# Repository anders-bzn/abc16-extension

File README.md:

# abc16-extension
The extension board needed in ABC80x when it shall be used with ABC16

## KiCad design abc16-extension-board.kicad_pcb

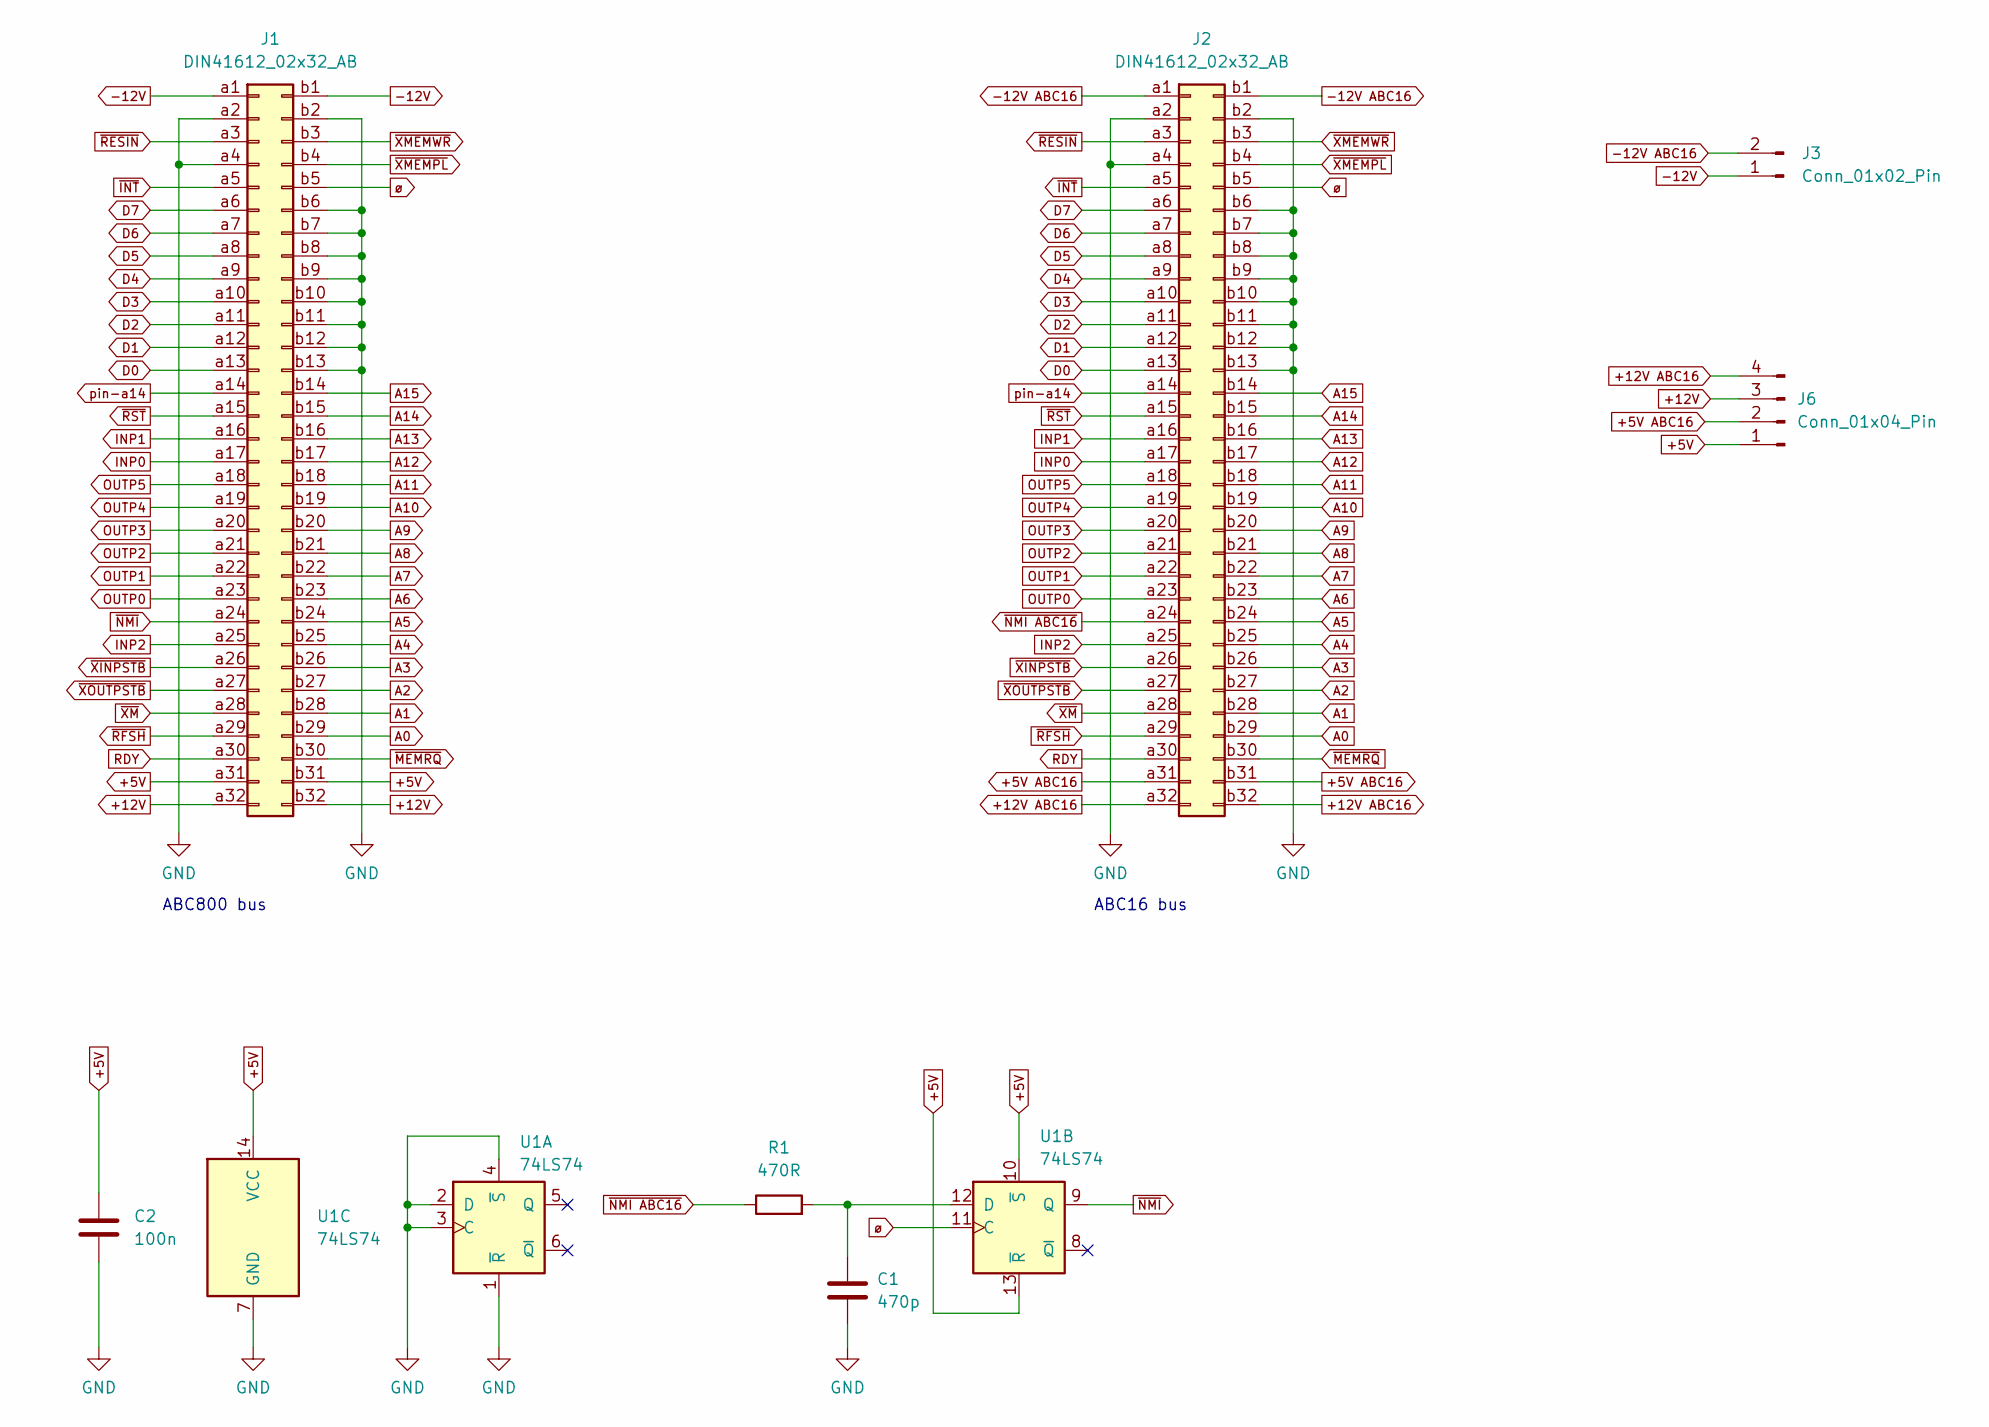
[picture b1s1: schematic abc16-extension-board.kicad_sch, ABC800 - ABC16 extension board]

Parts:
C1: 470p; C_Disc_D3.0mm_W1.6mm_P2.50mm
C2: 100n; C_Rect_L7.2mm_W2.5mm_P5.00mm_FKS2_FKP2_MKS2_MKP2
J1, J2: DIN41612_02x32_AB; DIN41612_B_2x32_Male_Horizontal_THT
J3: Conn_01x02_Pin; PinHeader_1x02_P2.54mm_Vertical
J6: Conn_01x04_Pin; PinHeader_2x02_P2.54mm_Vertical
R1: 470R; R_Axial_DIN0207_L6.3mm_D2.5mm_P10.16mm_Horizontal
U1: 74LS74; DIP-14_W7.62mm

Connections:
+5V: C2.1, J1.a31, J1.b31, J6.1, U1.10 (~S), U1.13 (~R), U1.14 (VCC)
+5V ABC16: J2.a31, J2.b31, J6.2
+12V: J1.a32, J1.b32, J6.3
+12V ABC16: J2.a32, J2.b32, J6.4
-12V: J1.a1, J1.b1, J3.1
-12V ABC16: J2.a1, J2.b1, J3.2
A0: J1.b29, J2.b29
A1: J1.b28, J2.b28
A2: J1.b27, J2.b27
A3: J1.b26, J2.b26
A4: J1.b25, J2.b25
A5: J1.b24, J2.b24
A6: J1.b23, J2.b23
A7: J1.b22, J2.b22
A8: J1.b21, J2.b21
A9: J1.b20, J2.b20
A10: J1.b19, J2.b19
A11: J1.b18, J2.b18
A12: J1.b17, J2.b17
A13: J1.b16, J2.b16
A14: J1.b15, J2.b15
A15: J1.b14, J2.b14
D0: J1.a13, J2.a13
D1: J1.a12, J2.a12
D2: J1.a11, J2.a11
D3: J1.a10, J2.a10
D4: J1.a9, J2.a9
D5: J1.a8, J2.a8
D6: J1.a7, J2.a7
D7: J1.a6, J2.a6
GND: C1.2, C2.2, J1.a2, J1.a4, J1.b2, J1.b6, J1.b7, J1.b8, J1.b9, J1.b10, J1.b11, J1.b12, J1.b13, J2.a2, J2.a4, J2.b2, J2.b6, J2.b7, J2.b8, J2.b9, J2.b10, J2.b11, J2.b12, J2.b13, U1.1 (~R), U1.2 (D), U1.3 (C), U1.4 (~S), U1.7 (GND)
INP0: J1.a17, J2.a17
INP1: J1.a16, J2.a16
INP2: J1.a25, J2.a25
unnamed: C1.1, R1.2, U1.12 (D)
OUTP0: J1.a23, J2.a23
OUTP1: J1.a22, J2.a22
OUTP2: J1.a21, J2.a21
OUTP3: J1.a20, J2.a20
OUTP4: J1.a19, J2.a19
OUTP5: J1.a18, J2.a18
RDY: J1.a30, J2.a30
pin-a14: J1.a14, J2.a14
~INT: J1.a5, J2.a5
~MEMRQ: J1.b30, J2.b30
~NMI ABC16: J2.a24, R1.1
~NMI: J1.a24, U1.9 (Q)
~RESIN: J1.a3, J2.a3
~RFSH: J1.a29, J2.a29
~RST: J1.a15, J2.a15
~XINPSTB: J1.a26, J2.a26
~XMEMPL: J1.b4, J2.b4
~XMEMWR: J1.b3, J2.b3
~XM: J1.a28, J2.a28
~XOUTPSTB: J1.a27, J2.a27
ø: J1.b5, J2.b5, U1.11 (C)

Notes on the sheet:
ABC800 bus
ABC16 bus

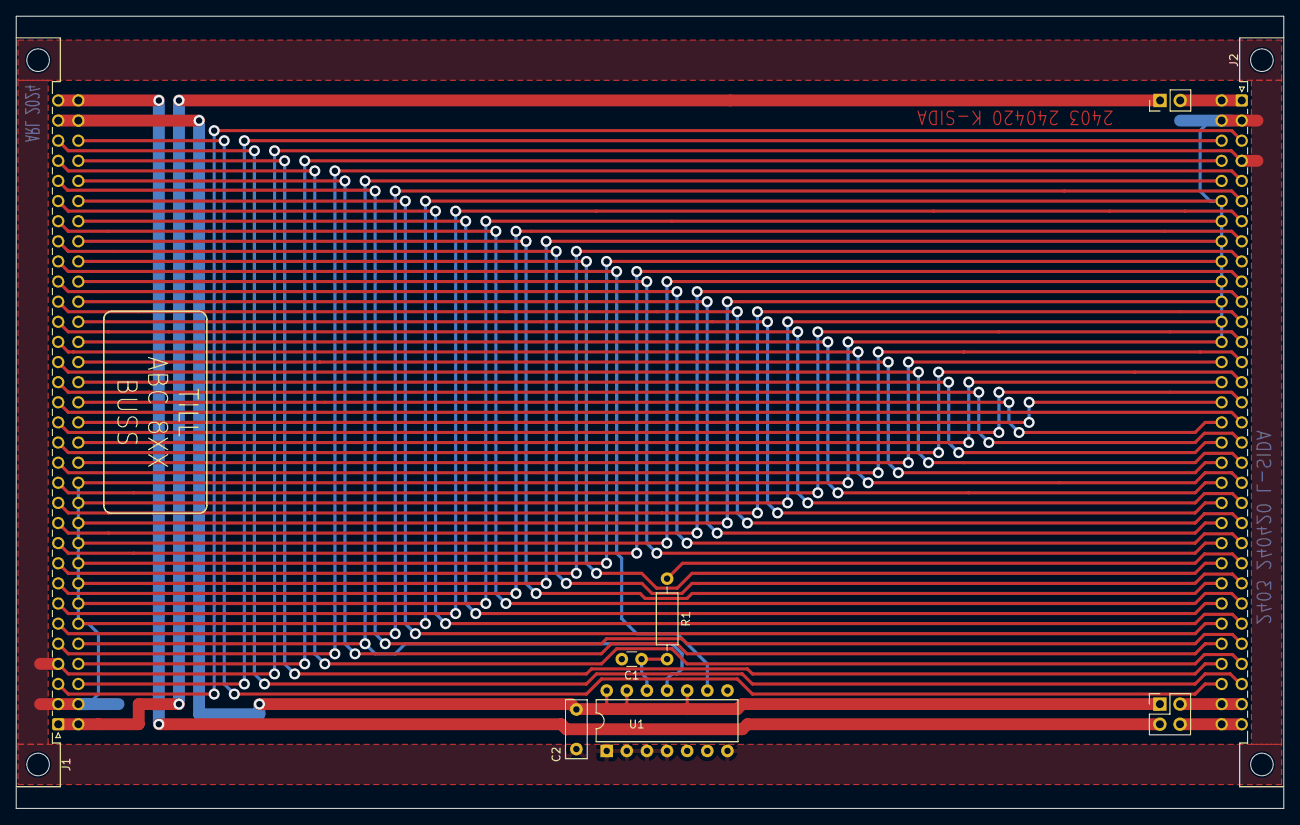
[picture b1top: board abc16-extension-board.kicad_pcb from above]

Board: 2 copper layers, 160.0 x 100.0 mm, 8 parts (0 on the bottom side), 56 nets.

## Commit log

2024-05-12 Added files
